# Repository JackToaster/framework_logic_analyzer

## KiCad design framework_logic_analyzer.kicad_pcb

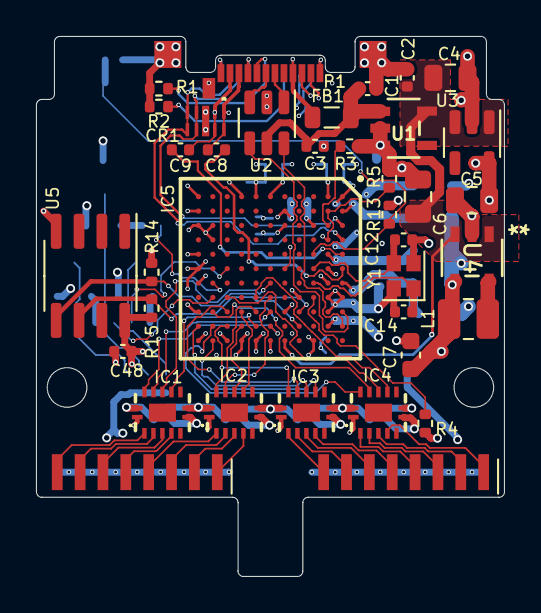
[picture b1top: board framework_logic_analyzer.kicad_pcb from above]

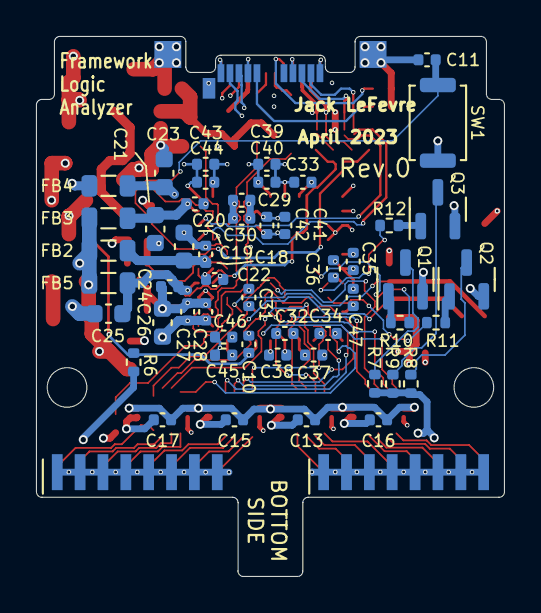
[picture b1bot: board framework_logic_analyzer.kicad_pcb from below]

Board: 4 copper layers, 26.0 x 30.0 mm, 94 parts (53 on the bottom side), 73 nets.

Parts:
C1, C2: 1u; C_0402_1005Metric
C3, C10, C11, C13, C15, C16, C17, C18, C20, C22, C24, C27, C29, C31, C32, C34, C36, C37, C39, C41, C43, C45, C47, C48: 100n; C_0402_1005Metric
C4, C5, C6: 10uF; C_0805_2012Metric
C7, C19, C21, C23, C25, C26: 22u; C_0603_1608Metric
C8, C9: 100n 25V; C_0402_1005Metric
C12, C14: 10p; C_0402_1005Metric
C28, C30, C33, C35, C38, C40, C42, C44, C46: 10n; C_0402_1005Metric
CR1: SP3010-04UTG; UDFEN-10_MO229_LTF
FB1: BLM21PG221SN1D; L_0805_2012Metric
FB2, FB3, FB4, FB5: MPZ2012S601A; L_0805_2012Metric
H1, H2: MountingHole; MountingHole_2.2mm_M2
IC1, IC2, IC3, IC4: TXU0104QWBQARQ1
IC5: CYUSB3014-BZXC; BGA121C80P11X11_1000X1000X120
J1, J2: Conn_02x08_Odd_Even; 20021311-00016T4LF
L1: 2.2u; L_1008_2520Metric
P1: USB_C_Plug; USB_C_Plug_Molex_105444
Q1, Q2, Q3: MMBT3904; SOT-23
R1, R2: 5.1k; R_0402_1005Metric
R3: 200R 1%; R_0402_1005Metric
R4: 6.04k 1%; R_0402_1005Metric
R5: 10k; R_0402_1005Metric
R6, R10, R11, R12: 1k; R_0402_1005Metric
R7, R14, R15: 2k; R_0402_1005Metric
R8: 560; R_0402_1005Metric
R9: 270; R_0402_1005Metric
R13: 100k; R_0402_1005Metric
SW1: SW_Push; SW_Push_SPST_NO_Alps_SKRK
TP1, TP2, TP3, TP4: TestPoint; TestPoint_Pad_1.5x1.5mm
U1: NCP360SNT1G; TSOP5_3X1P5_ONS
U2: WE-TVS-82400102; SOT-23-6
U3: AP2112K-3.3; SOT-23-5
U4: SC189CSKTRT; SOT_CSKTRT_SEM
U5: M24M02-DR; SOIC-8_3.9x4.9mm_P1.27mm
Y1: 19.200 MHz; Crystal_SMD_2016-4Pin_2.0x1.6mm

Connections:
+1V2: C7.1, C26.1, C27.1, C28.1, C29.1, C30.1, C31.1, C32.1, C33.1, C34.1, C35.1, C36.1, FB2.2, FB3.2, FB5.2, IC5.B10 (VDD_1), IC5.C3 (VDD_2), IC5.E9 (VDD_3), IC5.F11 (VDD_4), IC5.H1 (VDD_5), IC5.J11 (VDD_6), IC5.L5 (VDD_7), IC5.L7 (VDD_8), L1.2, U4.4 (VOUT)
+3.3V: C5.1, C13.1, C15.1, C16.1, C17.1, C37.1, C38.1, C39.1, C40.1, C41.1, C42.1, C43.1, C44.1, C45.1, C46.1, C47.1, C48.1, FB4.2, IC1.8 (OE), IC1.14 (VCCB), IC2.8 (OE), IC2.14 (VCCB), IC3.8 (OE), IC3.14 (VCCB), IC4.8 (OE), IC4.14 (VCCB), IC5.B1 (VIO4), IC5.C11 (VIO5), IC5.E3 (VIO3), IC5.F1 (VIO2), IC5.H11 (VIO1_1), IC5.L9 (VIO1_2), R13.1, R14.1, R15.1, U3.5 (VOUT), U5.8 (VCC)
/AVDD: C24.1, C25.1, FB5.1, IC5.A7 (AVDD)
/CH0: IC1.2 (A1), J1.1
/CH1: IC1.3 (A2), J1.3
/CH2: IC1.4 (A3), J1.5
/CH3: IC1.5 (A4), J1.7
/CH4: IC2.2 (A1), J1.9
/CH5: IC2.3 (A2), J1.11
/CH6: IC2.4 (A3), J1.13
/CH7: IC2.5 (A4), J1.15
/CH8: IC3.2 (A1), J2.1
/CH9: IC3.3 (A2), J2.3
/CH10: IC3.4 (A3), J2.5
/CH11: IC3.5 (A4), J2.7
/CH12: IC4.2 (A1), J2.9
/CH13: IC4.3 (A2), J2.11
/CH14: IC4.4 (A3), J2.13
/CH15: IC4.5 (A4), J2.15
/CVDDQ: C22.1, C23.1, FB4.1, IC5.B6 (CVDDQ)
/I2C_SCL: IC5.D9 (I2C_GPIO[58]), R14.2, U5.5 (SDA)
/I2C_SDA: IC5.D10 (I2C_GPIO[59]), R15.2, U5.6 (SCL)
/IN0: IC1.13 (B1Y), IC5.F10 (GPIO[0])
/IN1: IC1.12 (B2Y), IC5.F9 (GPIO[1])
/IN2: IC1.11 (B3Y), IC5.F7 (GPIO[2])
/IN3: IC1.10 (B4Y), IC5.G10 (GPIO[3])
/IN4: IC2.13 (B1Y), IC5.G9 (GPIO[4])
/IN5: IC2.12 (B2Y), IC5.F8 (GPIO[5])
/IN6: IC2.11 (B3Y), IC5.H10 (GPIO[6])
/IN7: IC2.10 (B4Y), IC5.H9 (GPIO[7])
/IN8: IC3.13 (B1Y), IC5.J10 (GPIO[8])
/IN9: IC3.12 (B2Y), IC5.J9 (GPIO[9])
/IN10: IC3.11 (B3Y), IC5.K11 (GPIO[10])
/IN11: IC3.10 (B4Y), IC5.L10 (GPIO[11])
/IN12: IC4.13 (B1Y), IC5.K10 (GPIO[12])
/IN13: IC4.12 (B2Y), IC5.K9 (GPIO[13])
/IN14: IC4.11 (B3Y), IC5.J8 (GPIO[14])
/IN15: IC4.10 (B4Y), IC5.G8 (GPIO[15])
/U3RX_VDDQ: C20.1, C21.1, FB3.1, IC5.A2 (U3RXVDDQ)
/U3TX_VDDQ: C18.1, C19.1, FB2.1, IC5.B5 (U3TXVDDQ)
/USB-C/SSD+: P1.A6 (D+), U2.3
/USB-C/SSD-: P1.A7 (D-), U2.1
/USB-C/SS_D+: IC5.A9 (DP), U2.4
/USB-C/SS_D-: IC5.A10 (DM), U2.6
/USB-C/SS_RX+: CR1.5, CR1.6, IC5.A4 (SSRXP), P1.A11 (RX2+), P1.B11 (RX1+)
/USB-C/SS_RX-: CR1.4, CR1.7, IC5.A3 (SSRXM), P1.A10 (RX2-), P1.B10 (RX1-)
/USB-C/SS_TX+: C9.1, CR1.2, CR1.9, P1.A2 (TX1+), P1.B2 (TX2+)
/USB-C/SS_TX-: C8.1, CR1.1, CR1.10, P1.A3 (TX1-), P1.B3 (TX2-)
/USB-C/VBUS_IN: C1.1, C3.1, FB1.2, U1.1 (IN), U2.5
GND: C1.2, C2.2, C3.2, C4.2, C5.2, C6.2, C7.2, C10.2, C11.2, C12.2, C13.2, C14.2, C15.2, C16.2, C17.2, C18.2, C19.2, C20.2, C21.2, C22.2, C23.2, C24.2, C25.2, C26.2, C27.2, C28.2, C29.2, C30.2, C31.2, C32.2, C33.2, C34.2, C35.2, C36.2, C37.2, C38.2, C39.2, C40.2, C41.2, C42.2, C43.2, C44.2, C45.2, C46.2, C47.2, C48.2, CR1.3, CR1.8, IC1.7 (GND), IC2.7 (GND), IC3.7 (GND), IC4.7 (GND), IC5.A1 (U3VSSQ), IC5.A8 (VSS_1), IC5.B7 (AVSS), IC5.B8 (VSS_2), IC5.B9 (VSS_3), IC5.D8 (VSS_4), IC5.E2 (VSS_5), IC5.G1 (VSS_6), IC5.G11 (VSS_7), IC5.K3 (VSS_8), IC5.K4 (VSS_9), IC5.L1 (VSS_10), IC5.L2 (VSS_11), IC5.L3 (VSS_12), IC5.L6 (VSS_13), IC5.L11 (VSS_14), J1.2, J1.4, J1.6, J1.8, J1.10, J1.12, J1.14, J1.16, J2.2, J2.4, J2.6, J2.8, J2.10, J2.12, J2.14, J2.16, P1.A1 (GND), P1.A12 (GND), P1.B1 (GND), P1.B12 (GND), P1.S1 (SHIELD), Q1.2 (E), Q2.2 (E), Q3.2 (E), R1.2, R2.2, R3.1, R4.1, R5.2, SW1.1, TP1.1, TP2.1, TP3.1, TP4.1, U1.2 (GND), U1.3 (*EN), U2.2, U3.2 (GND), U4.2 (GND), U5.4 (VSS), Y1.2, Y1.4
unnamed: FB1.1, P1.A4 (VBUS), P1.A9 (VBUS), P1.B4 (VBUS), P1.B9 (VBUS)
unnamed: IC5.B2 (FSLC[0]), IC5.B4 (FSLC[1]), IC5.E6 (FSLC[2]), R5.1
unnamed: C11.1, IC5.C5 (RESET#), R13.2, SW1.2
unnamed: IC5.C8 (R_USB2), R4.2
unnamed: IC5.B3 (R_USB3), R3.2
unnamed: C8.2, IC5.A6 (SSTXM)
unnamed: C9.2, IC5.A5 (SSTXP)
unnamed: C12.1, IC5.C6 (XTALIN), Y1.3
unnamed: C14.1, IC5.C7 (XTALOUT), Y1.1
unnamed: P1.A5 (CC), R1.1
unnamed: P1.B5 (VCONN), R2.1
unnamed: Q1.1 (B), R10.2
unnamed: Q1.3 (C), R7.2
unnamed: Q2.1 (B), R11.2
unnamed: Q2.3 (C), R8.2
unnamed: Q3.1 (B), R12.2
unnamed: Q3.3 (C), R9.2
unnamed: L1.1, U4.5 (LX)
VBUS: C2.1, C4.1, C6.1, C10.1, IC5.E11 (VBUS), R6.1, U1.5 (OUT), U3.1 (VIN), U3.3 (EN), U4.1 (VIN), U4.3 (EN)
VIO: IC1.1 (VCCA), IC2.1 (VCCA), IC3.1 (VCCA), IC4.1 (VCCA), R6.2, R7.1, R8.1, R9.1
VS1: IC5.J6 (GPIO[16]), R10.1
VS2: IC5.K8 (GPIO[17]), R11.1
VS3: IC5.K7 (GPIO[18]), R12.1

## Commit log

2023-04-21 New header and enclosure
2023-04-25 Remove jtag header, add reset button
2023-05-29 added part nums
2023-05-29 Added kicad ci/cd workflow
2023-05-29 try to fix cicd
2023-05-29 try to fix cicd again
2023-05-30 fixed things
2023-05-30 update erc checks

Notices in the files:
framework_logic_analyzer.kicad_pcb:
This work is licensed under a Creative Commons Attribution 4.0 International License
